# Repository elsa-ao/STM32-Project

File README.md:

# STM32F103C8T6 Custom Dev Board

Custom STM32F103C8T6 USB dev board, designed from scratch in STM32CubeMX (pinout) and KiCad (schematic + PCB), following Phil's STM32 Udemy course.

## Features

- STM32F103C8T6, powered over USB (AMS1117-3.3 regulator)
- Native USB device (Micro-B connector)
- UART and I²C broken out to headers
- SWD header for programming/debugging
- 16MHz crystal, BOOT0 select switch, power LED

## Repository structure

```
stm32-udemy-project/
├── cubemx/   # STM32CubeMX .ioc project
├── kicad/    # KiCad schematic + PCB
└── docs/     # Exported images/renders
```

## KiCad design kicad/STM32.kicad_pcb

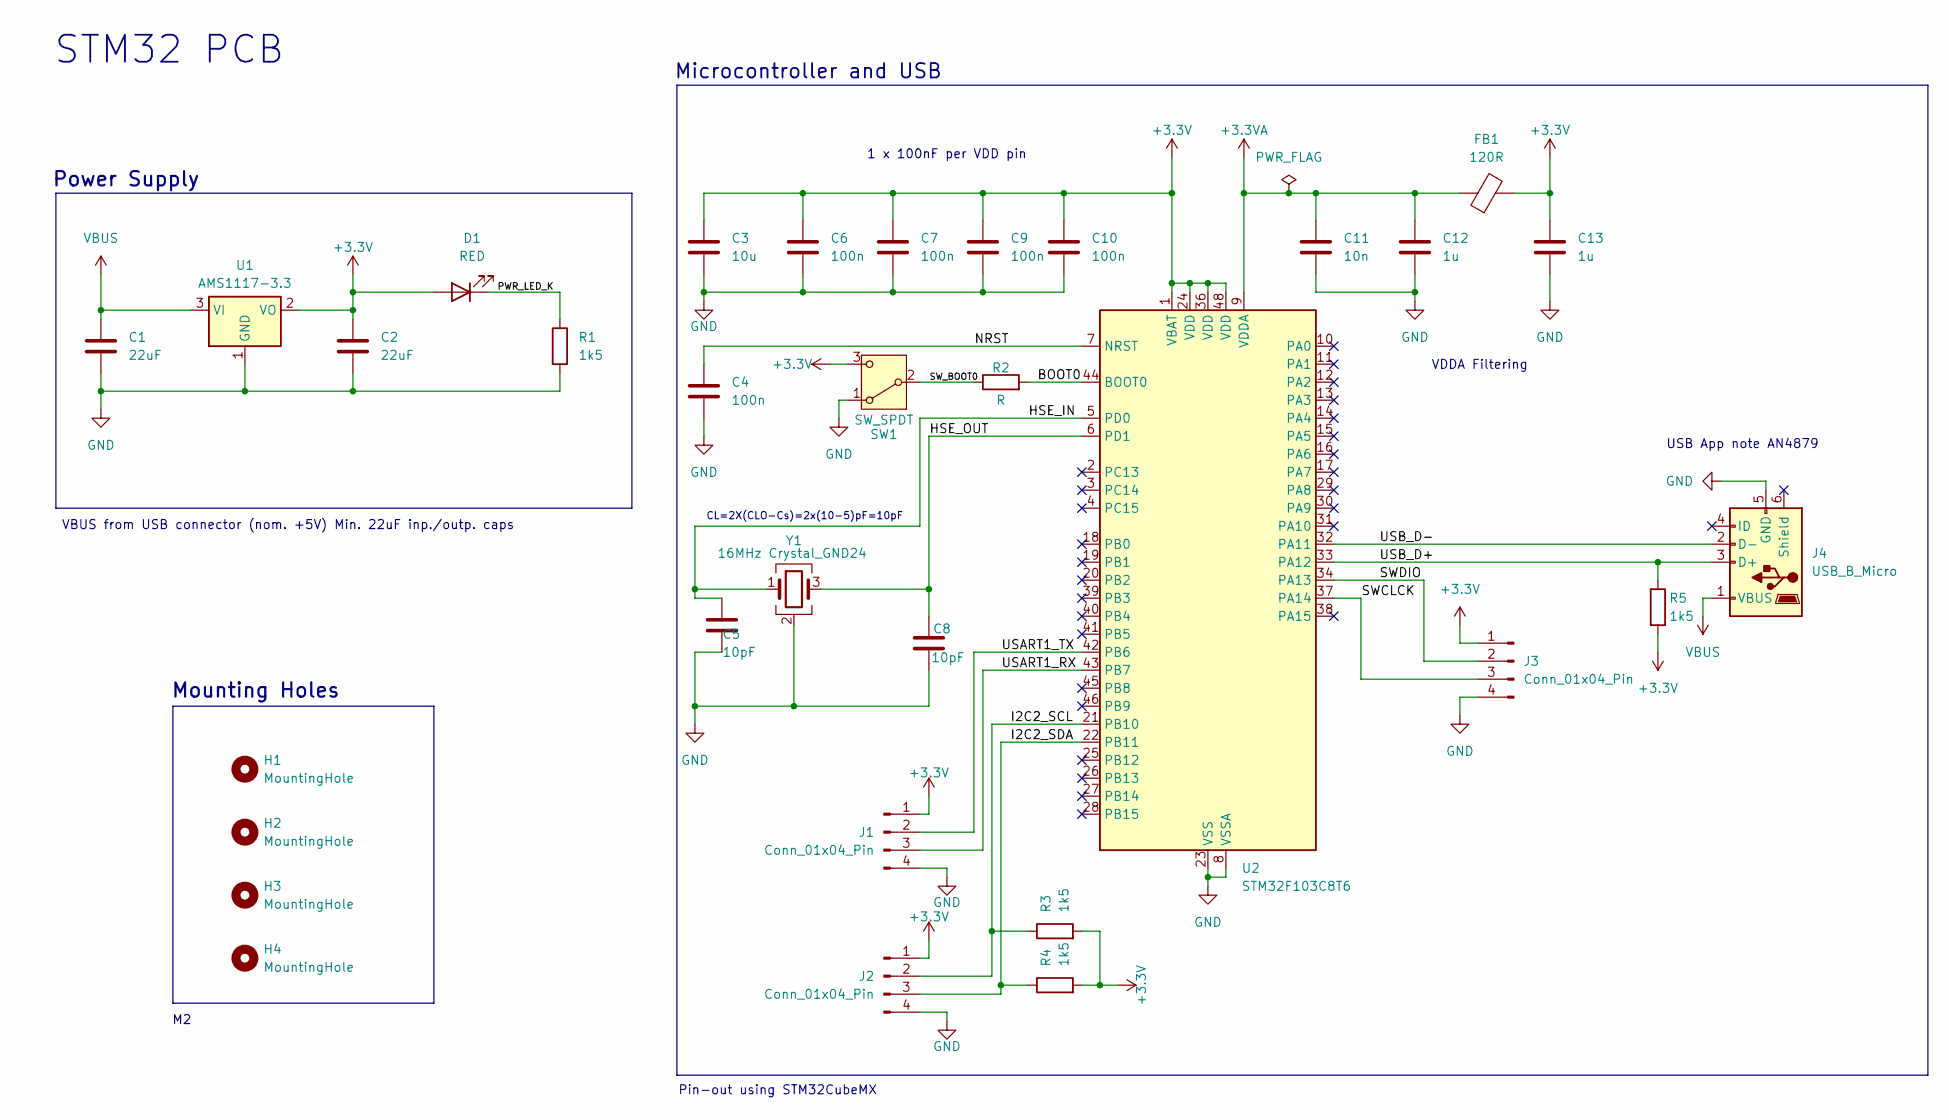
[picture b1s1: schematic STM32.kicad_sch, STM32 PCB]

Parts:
C1, C2: 22uF; C_0805_2012Metric
C3: 10u; C_0603_1608Metric
C4, C6, C7, C9, C10: 100n; C_0402_1005Metric
C5, C8: 10pF; C_0402_1005Metric
C11: 10n; C_0402_1005Metric
C12, C13: 1u; C_0402_1005Metric
D1: RED; LED_0603_1608Metric
FB1: 120R; L_0603_1608Metric
H1, H2, H3, H4: MountingHole; MountingHole_2.2mm_M2
J1, J2, J3: Conn_01x04_Pin; PinHeader_1x04_P2.54mm_Vertical
J4: USB_B_Micro; USB_Micro-B_Wuerth_629105150521
R1, R3, R4, R5: 1k5; R_0402_1005Metric
R2: R; R_0402_1005Metric
SW1: SW_SPDT; SW_SPDT_PCM12
U1: AMS1117-3.3; SOT-223-3_TabPin2
U2: STM32F103C8T6; LQFP-48_7x7mm_P0.5mm
Y1: 16MHz Crystal_GND24; Crystal_SMD_3225-4Pin_3.2x2.5mm

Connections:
+3.3V: C2.1, C3.1, C6.1, C7.1, C9.1, C10.1, C13.1, D1.2 (A), FB1.2, J1.1, J2.1, J3.1, R3.2, R4.2, R5.2, SW1.3 (C), U1.2 (VO), U2.1 (VBAT), U2.24 (VDD), U2.36 (VDD), U2.48 (VDD); also elsewhere on the board
+3.3VA: C11.1, C12.1, FB1.1, U2.9 (VDDA)
/BOOT0: R2.2, U2.44 (BOOT0)
/HSE_IN: C5.1, U2.5 (PD0), Y1.1
/HSE_OUT: C8.1, U2.6 (PD1), Y1.3
/I2C2_SCL: J2.2, R3.1, U2.21 (PB10)
/I2C2_SDA: J2.3, R4.1, U2.22 (PB11)
/NRST: C4.1, U2.7 (NRST)
/PWR_LED_K: D1.1 (K), R1.1
/SWCLCK: J3.3, U2.37 (PA14)
/SWDIO: J3.2, U2.34 (PA13)
/SW_BOOT0: R2.1, SW1.2 (B); also elsewhere on the board
/USART1_RX: J1.3, U2.43 (PB7)
/USART1_TX: J1.2, U2.42 (PB6)
/USB_D+: J4.3 (D+), R5.1, U2.33 (PA12)
/USB_D-: J4.2 (D-), U2.32 (PA11)
GND: C1.2, C2.2, C3.2, C4.2, C5.2, C6.2, C7.2, C8.2, C9.2, C10.2, C11.2, C12.2, C13.2, J1.4, J2.4, J3.4, J4.5 (GND), R1.2, SW1.1 (A), U1.1 (GND), U2.8 (VSSA), U2.23 (VSS), U2.35 (VSS), U2.47 (VSS), Y1.2 (G), Y1.4 (G); also elsewhere on the board
VBUS: C1.1, J4.1 (VBUS), U1.3 (VI)

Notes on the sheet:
Mounting Holes
STM32 PCB
Power Supply
Pin-out using STM32CubeMX
VDDA Filtering
Microcontroller and USB
1 x 100nF per VDD pin
CL=2X(CLO-Cs)=2x(10-5)pF=10pF
USB App note AN4879
VBUS from USB connector (nom. +5V) Min. 22uF inp./outp. caps

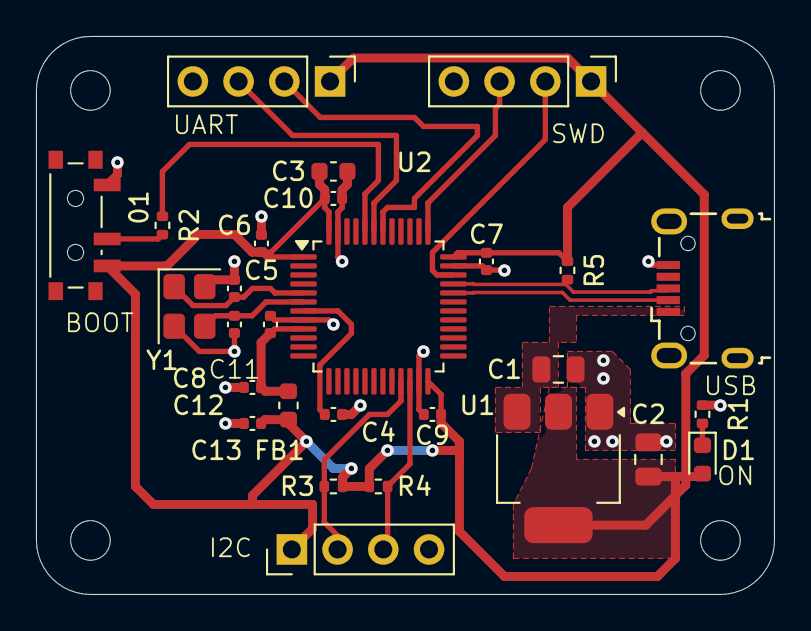
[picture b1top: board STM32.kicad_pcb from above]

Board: 2 copper layers, 41.0 x 31.0 mm, 32 parts (0 on the bottom side), 18 nets.

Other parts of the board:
01: SW_SPDT; SW_SPDT_PCM12

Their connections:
+3.3V: 01.3 (C); also elsewhere on the board
/SW_BOOT0: 01.2 (B); also elsewhere on the board
GND: 01.1 (A); also elsewhere on the board

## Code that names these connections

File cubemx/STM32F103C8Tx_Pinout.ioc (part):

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Mcu.Name=STM32F103C(8-B)Tx
Mcu.Package=LQFP48
Mcu.UserName=STM32F103C8Tx
PA11.Mode=Device
PA11.Signal=USB_DM
PA12.Mode=Device
PA12.Signal=USB_DP
PA13.Mode=Serial_Wire
PA13.Signal=SYS_JTMS-SWDIO
PA14.Mode=Serial_Wire
PA14.Signal=SYS_JTCK-SWCLK
PB10.Mode=I2C
PB10.Signal=I2C2_SCL
PB11.Mode=I2C
PB11.Signal=I2C2_SDA
PB6.Mode=Asynchronous
PB6.Signal=USART1_TX
PB7.Mode=Asynchronous
PB7.Signal=USART1_RX
PD0-OSC_IN.Mode=HSE-External-Oscillator
PD0-OSC_IN.Signal=RCC_OSC_IN
PD1-OSC_OUT.Mode=HSE-External-Oscillator
PD1-OSC_OUT.Signal=RCC_OSC_OUT
board=custom
